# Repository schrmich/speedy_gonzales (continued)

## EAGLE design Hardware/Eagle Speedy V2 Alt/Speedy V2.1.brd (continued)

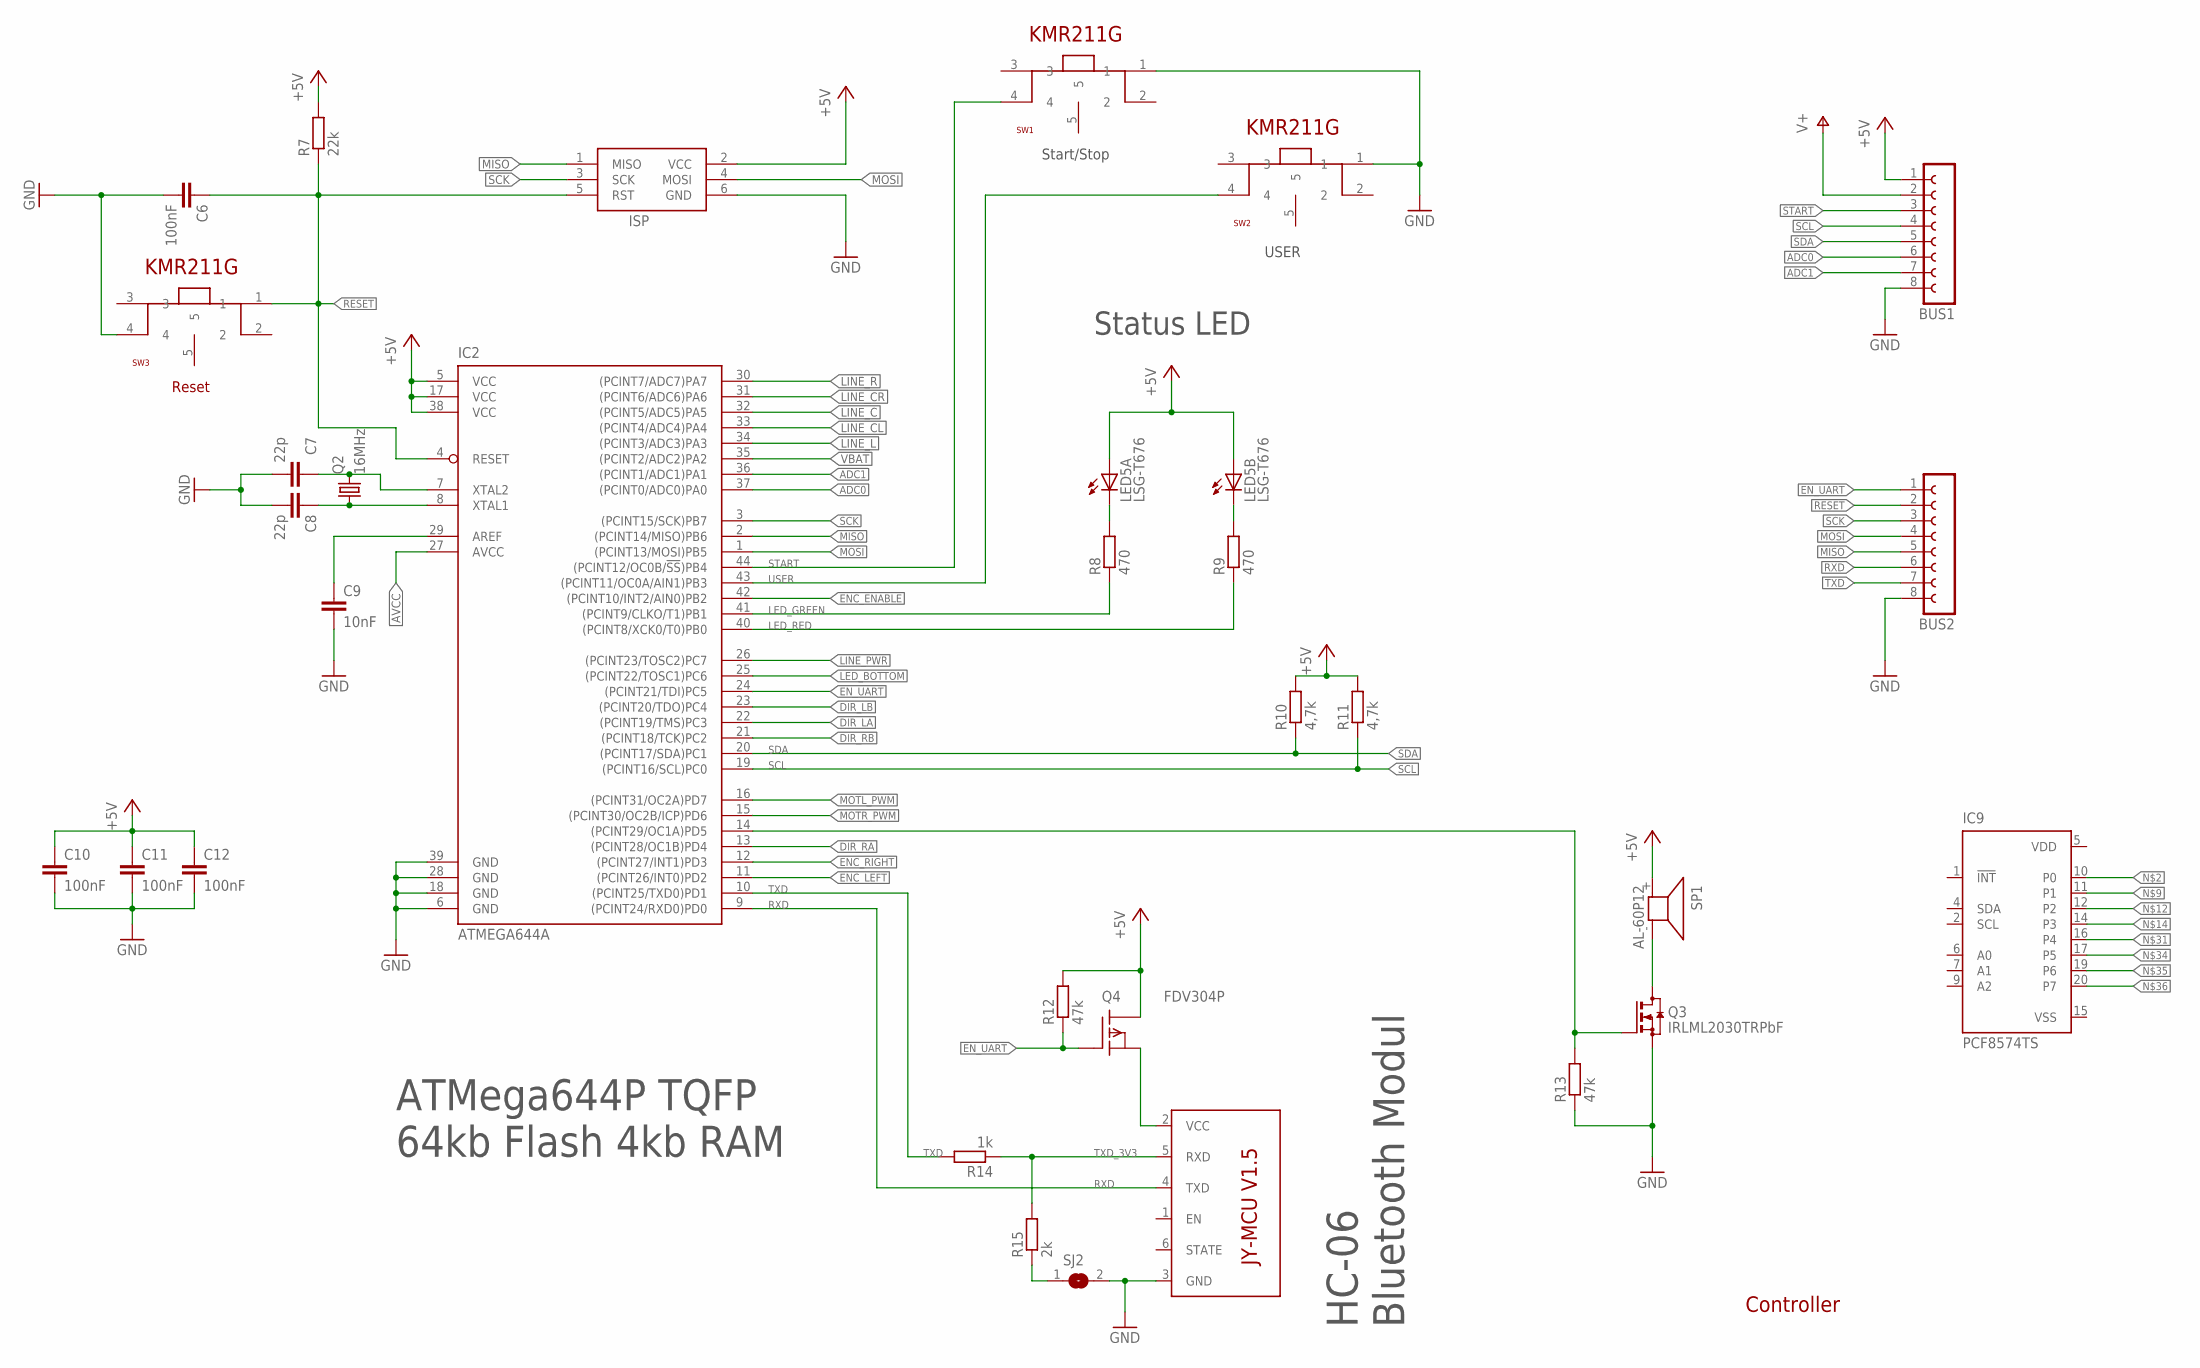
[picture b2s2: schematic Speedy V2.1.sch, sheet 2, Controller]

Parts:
BUS1, BUS2: FE08-1; FE08
C6: 100nF; C0805
C7, C8: 22p; C0603
C9: 10nF; C0603
C10, C11, C12: 100nF; C0603
IC2: ATMEGA644A; TQFP44
IC9: PCF8574TS; SSOP20
ISP: AVRISP-6; AVRISP
LED5: LSG-T676; P-LCC4-0
Q2: 16MHz; 7X5MMQUARZ
Q3: IRLML2030TRPbF; SOT23
Q4: FDV304P; SOT23
R7: 22k; R0805
R8, R9: 470; R0805
R10, R11: 4,7k; R0805
R12, R13: 47k; R0805
R14: 1k; R0805
R15: 2k; R0805
SJ2: SJ
SP1: AL-60P12; KSS1201
SW1, SW2, SW3: KMR211G_SWITCH
U1: BT_BOARD

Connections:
+5V: BUS1.1, C10.1, C11.1, C12.1, IC2.5 (VCC), IC2.17 (VCC), IC2.38 (VCC), ISP.2 (VCC), LED5.2 (A), LED5.4 (A), Q4.D, R7.2, R10.2, R11.2, R12.2, SP1.+ (1); also elsewhere on the board
ADC0: BUS1.6, IC2.37 ((PCINT0/ADC0)PA0)
ADC1: BUS1.7, IC2.36 ((PCINT1/ADC1)PA1)
AVCC: IC2.27 (AVCC); also elsewhere on the board
BUZZER: IC2.14 ((PCINT29/OC1A)PD5), Q3.1 (G), R13.2
DIR_LA: IC2.22 ((PCINT19/TMS)PC3); also elsewhere on the board
DIR_LB: IC2.23 ((PCINT20/TDO)PC4); also elsewhere on the board
DIR_RA: IC2.13 ((PCINT28/OC1B)PD4); also elsewhere on the board
DIR_RB: IC2.21 ((PCINT18/TCK)PC2); also elsewhere on the board
ENC_ENABLE: IC2.42 ((PCINT10/INT2/AIN0)PB2)
ENC_LEFT: IC2.11 ((PCINT26/INT0)PD2)
ENC_RIGHT: IC2.12 ((PCINT27/INT1)PD3)
EN_UART: BUS2.1, IC2.24 ((PCINT21/TDI)PC5), Q4.G, R12.1
GND: BUS1.8, BUS2.8, C6.2, C7.2, C8.2, C9.2, C10.2, C11.2, C12.2, IC2.6 (GND), IC2.18 (GND), IC2.28 (GND), IC2.39 (GND), ISP.6 (GND), Q3.2 (S), R13.1, SJ2.2, SW1.1, SW2.1, SW3.4, U1.3 (GND); also elsewhere on the board
LED_BOTTOM: IC2.25 ((PCINT22/TOSC1)PC6); also elsewhere on the board
LED_GREEN: IC2.41 ((PCINT9/CLKO/T1)PB1), R8.1
LED_RED: IC2.40 ((PCINT8/XCK0/T0)PB0), R9.1
LINE_C: IC2.32 ((PCINT5/ADC5)PA5); also elsewhere on the board
LINE_CL: IC2.33 ((PCINT4/ADC4)PA4); also elsewhere on the board
LINE_CR: IC2.31 ((PCINT6/ADC6)PA6); also elsewhere on the board
LINE_L: IC2.34 ((PCINT3/ADC3)PA3); also elsewhere on the board
LINE_PWR: IC2.26 ((PCINT23/TOSC2)PC7); also elsewhere on the board
LINE_R: IC2.30 ((PCINT7/ADC7)PA7); also elsewhere on the board
MISO: BUS2.5, IC2.2 ((PCINT14/MISO)PB6), ISP.1 (MISO)
MOSI: BUS2.4, IC2.1 ((PCINT13/MOSI)PB5), ISP.4 (MOSI)
MOTL_PWM: IC2.16 ((PCINT31/OC2A)PD7); also elsewhere on the board
MOTR_PWM: IC2.15 ((PCINT30/OC2B/ICP)PD6); also elsewhere on the board
unnamed: Q3.3 (D), SP1.- (2)
unnamed: LED5.1 (C), R8.2
unnamed: C9.1, IC2.29 (AREF)
unnamed: R15.1, SJ2.1
unnamed: LED5.3 (C), R9.2
unnamed: Q4.S, U1.2 (VCC)
unnamed: C7.1, IC2.7 (XTAL2), Q2.P$3 (2)
unnamed: C8.1, IC2.8 (XTAL1), Q2.P$1 (1)
RESET: BUS2.2, C6.1, IC2.4 (RESET), ISP.5 (RST), R7.1, SW3.1; also elsewhere on the board
RXD: BUS2.6, IC2.9 ((PCINT24/RXD0)PD0), U1.4 (TXD)
SCK: BUS2.3, IC2.3 ((PCINT15/SCK)PB7), ISP.3 (SCK)
SCL: BUS1.4, IC2.19 ((PCINT16/SCL)PC0), R11.1
SDA: BUS1.5, IC2.20 ((PCINT17/SDA)PC1), R10.1
START: BUS1.3, IC2.44 ((PCINT12/OC0B/!SS!)PB4), SW1.4
TXD: BUS2.7, IC2.10 ((PCINT25/TXD0)PD1), R14.2
TXD_3V3: R14.1, R15.2, U1.5 (RXD)
USER: IC2.43 ((PCINT11/OC0A/AIN1)PB3), SW2.4
V+: BUS1.2; also elsewhere on the board
VBAT: IC2.35 ((PCINT2/ADC2)PA2); also elsewhere on the board
VDD: IC9.5 (VDD)
VSS: IC9.15 (VSS)

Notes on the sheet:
Controller
Start/Stop
Reset
HC-06 Bluetooth Modul
ATMega644P TQFP 64kb Flash 4kb RAM
USER
Status LED

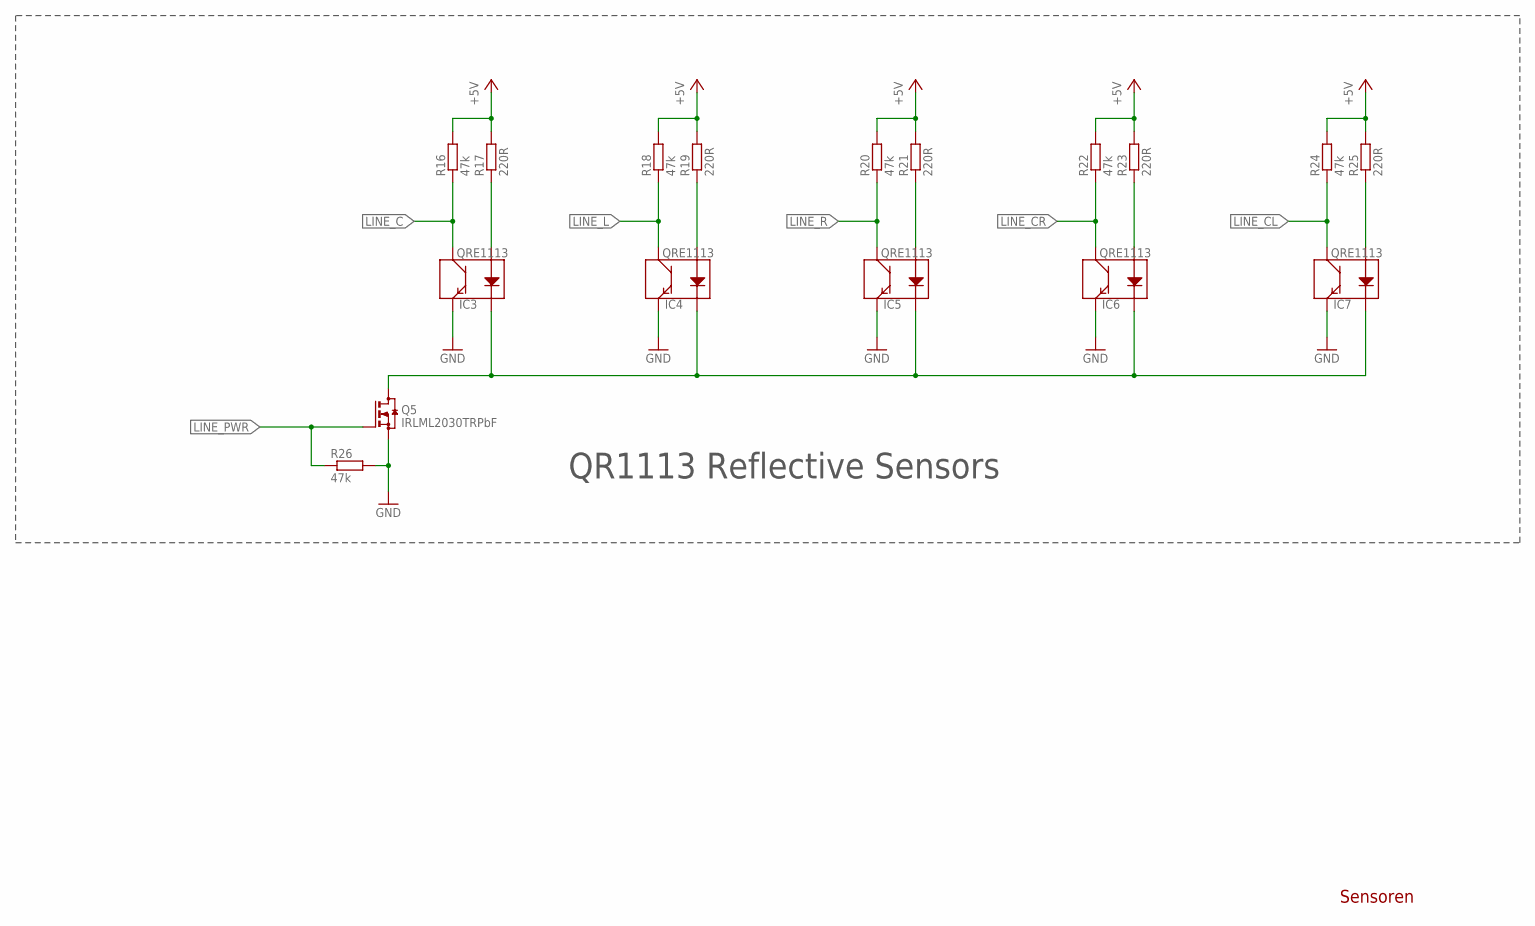
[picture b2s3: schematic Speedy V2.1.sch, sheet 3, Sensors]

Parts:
IC3, IC4, IC5, IC6, IC7: QRE1113
Q5: IRLML2030TRPbF; SOT23
R16, R18, R20, R22, R24, R26: 47k; R0805
R17, R19, R21, R23, R25: 220R; R0805

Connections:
+5V: R16.2, R17.2, R18.2, R19.2, R20.2, R21.2, R22.2, R23.2, R24.2, R25.2; also elsewhere on the board
GND: IC3.4 (E), IC4.4 (E), IC5.4 (E), IC6.4 (E), IC7.4 (E), Q5.2 (S), R26.2; also elsewhere on the board
LINE_C: IC3.3 (C), R16.1; also elsewhere on the board
LINE_CL: IC7.3 (C), R24.1; also elsewhere on the board
LINE_CR: IC6.3 (C), R22.1; also elsewhere on the board
LINE_L: IC4.3 (C), R18.1; also elsewhere on the board
LINE_PWR: Q5.1 (G), R26.1; also elsewhere on the board
LINE_R: IC5.3 (C), R20.1; also elsewhere on the board
unnamed: IC3.2 (K), IC4.2 (K), IC5.2 (K), IC6.2 (K), IC7.2 (K), Q5.3 (D)
unnamed: IC4.1 (A), R19.1
unnamed: IC3.1 (A), R17.1
unnamed: IC5.1 (A), R21.1
unnamed: IC6.1 (A), R23.1
unnamed: IC7.1 (A), R25.1

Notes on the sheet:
Sensoren
QR1113 Reflective Sensors

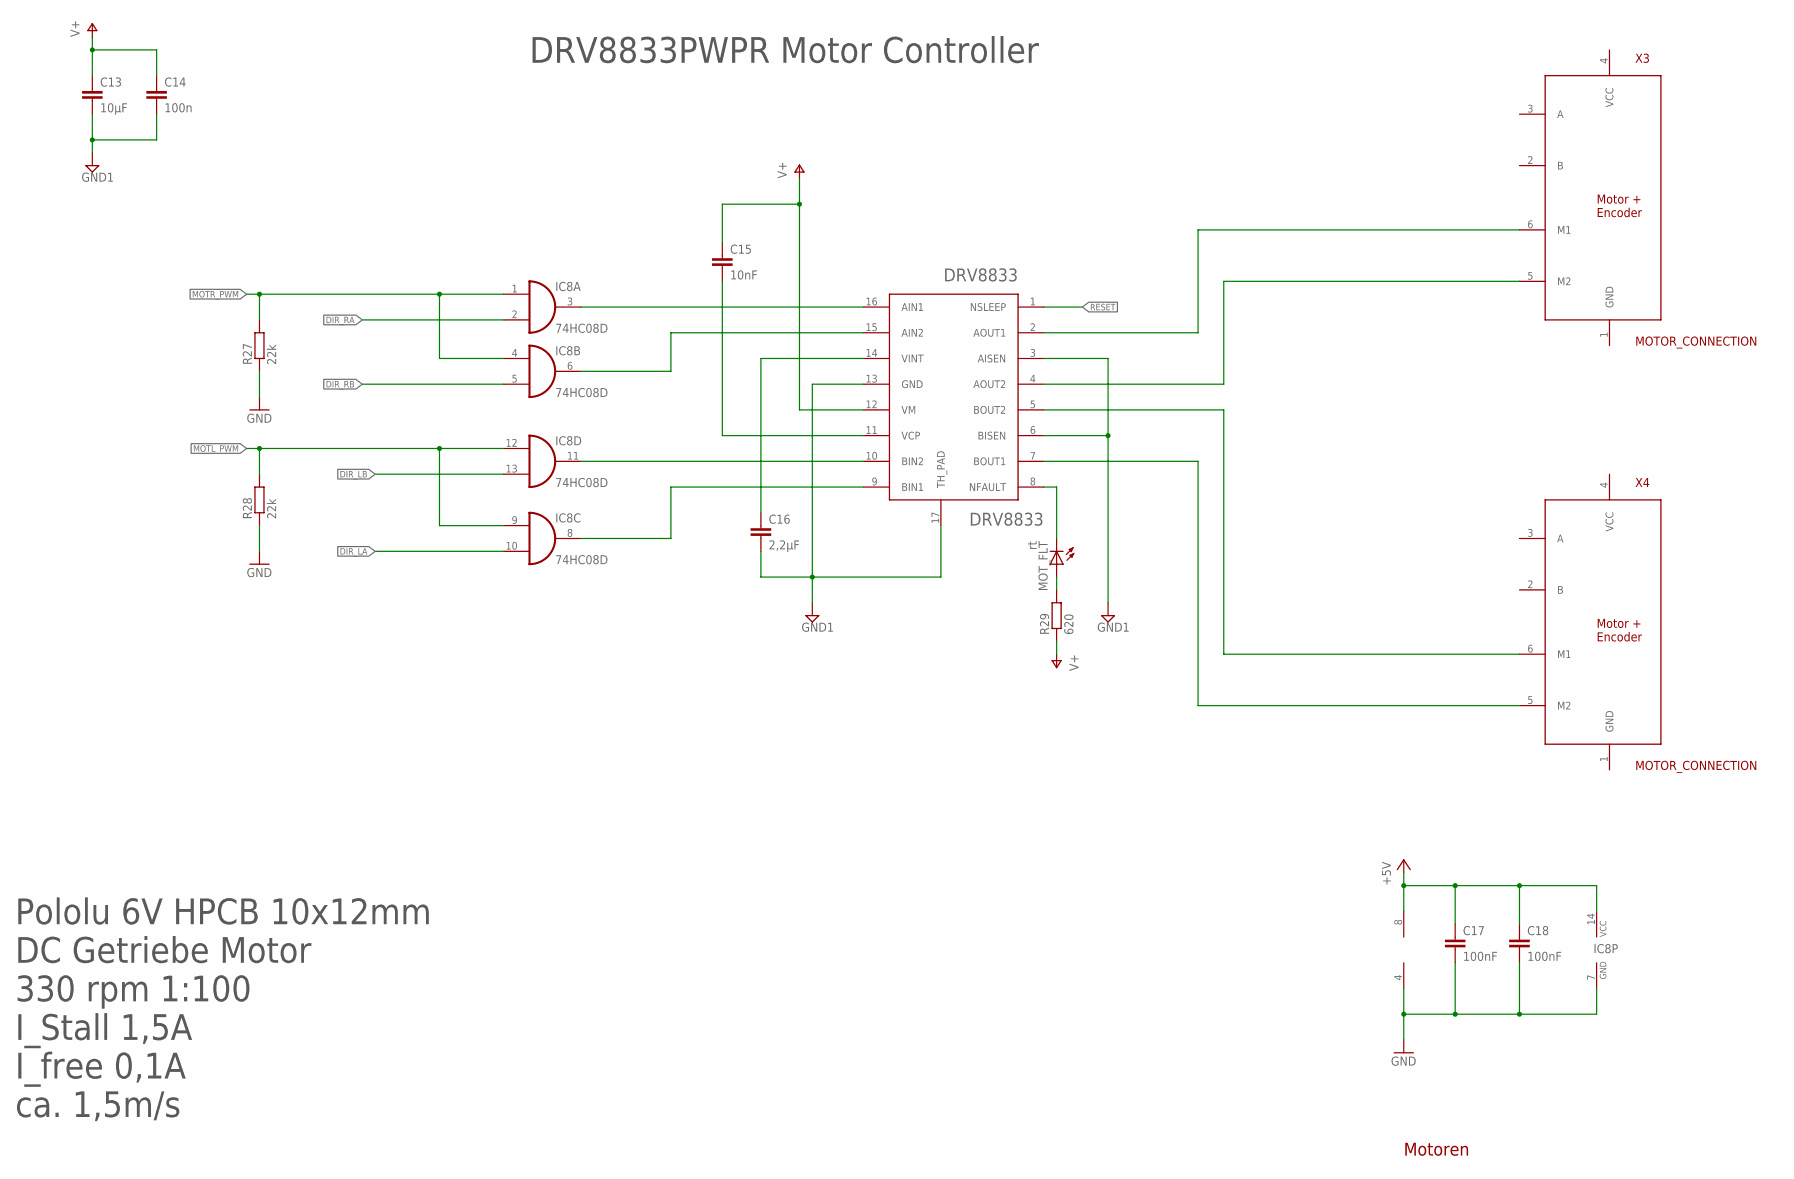
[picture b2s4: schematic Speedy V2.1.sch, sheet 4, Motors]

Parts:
C13: 10µF; C1206
C14: 100n; C0805
C15: 10nF; C0805
C16: 2,2µF; C1206
C17, C18: 100nF; C0805
IC8: 74HC08D; SO14
IC11: LM358D; SO08
MOT_FLT: rt; CHIP-LED0805
R27, R28: 22k; R0805
R29: 620; R0805
U3: DRV8833; SOP65P640X120-17N
X3, X4: MOTOR_CONNECTION; 2X03

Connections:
+5V: C17.1, C18.1, IC8.14 (VCC), IC11.8 (V+); also elsewhere on the board
DIR_LA: IC8.10 (I1); also elsewhere on the board
DIR_LB: IC8.13 (I1); also elsewhere on the board
DIR_RA: IC8.2 (I1); also elsewhere on the board
DIR_RB: IC8.5 (I1); also elsewhere on the board
GND: C17.2, C18.2, IC8.7 (GND), IC11.4 (V-), R27.1, R28.1; also elsewhere on the board
GND1: C13.2, C14.2, C16.2, U3.3 (AISEN), U3.6 (BISEN), U3.13 (GND), U3.17 (TH_PAD); also elsewhere on the board
MOTL_PWM: IC8.9 (I0), IC8.12 (I0), R28.2; also elsewhere on the board
MOTR_PWM: IC8.1 (I0), IC8.4 (I0), R27.2; also elsewhere on the board
unnamed: C16.1, U3.14 (VINT)
unnamed: C15.2, U3.11 (VCP)
unnamed: U3.5 (BOUT2), X4.6 (M1)
unnamed: MOT_FLT.A, R29.2
unnamed: MOT_FLT.C, U3.8 (NFAULT)
unnamed: IC8.3 (O), U3.16 (AIN1)
unnamed: IC8.6 (O), U3.15 (AIN2)
unnamed: IC8.11 (O), U3.10 (BIN2)
unnamed: IC8.8 (O), U3.9 (BIN1)
unnamed: U3.7 (BOUT1), X4.5 (M2)
unnamed: U3.4 (AOUT2), X3.5 (M2)
unnamed: U3.2 (AOUT1), X3.6 (M1)
RESET: U3.1 (NSLEEP); also elsewhere on the board
V+: C13.1, C14.1, C15.1, R29.1, U3.12 (VM); also elsewhere on the board

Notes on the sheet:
Motoren
DRV8833PWPR Motor Controller
Pololu 6V HPCB 10x12mm DC Getriebe Motor 330 rpm 1:100 I_Stall 1,5A I_free 0,1A ca. 1,5m/s

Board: 2 copper layers, 91 parts (23 on the bottom side), 71 nets, no tracks yet.

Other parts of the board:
U$1: FUTURA_V1.0_MOTOT_MOUNT

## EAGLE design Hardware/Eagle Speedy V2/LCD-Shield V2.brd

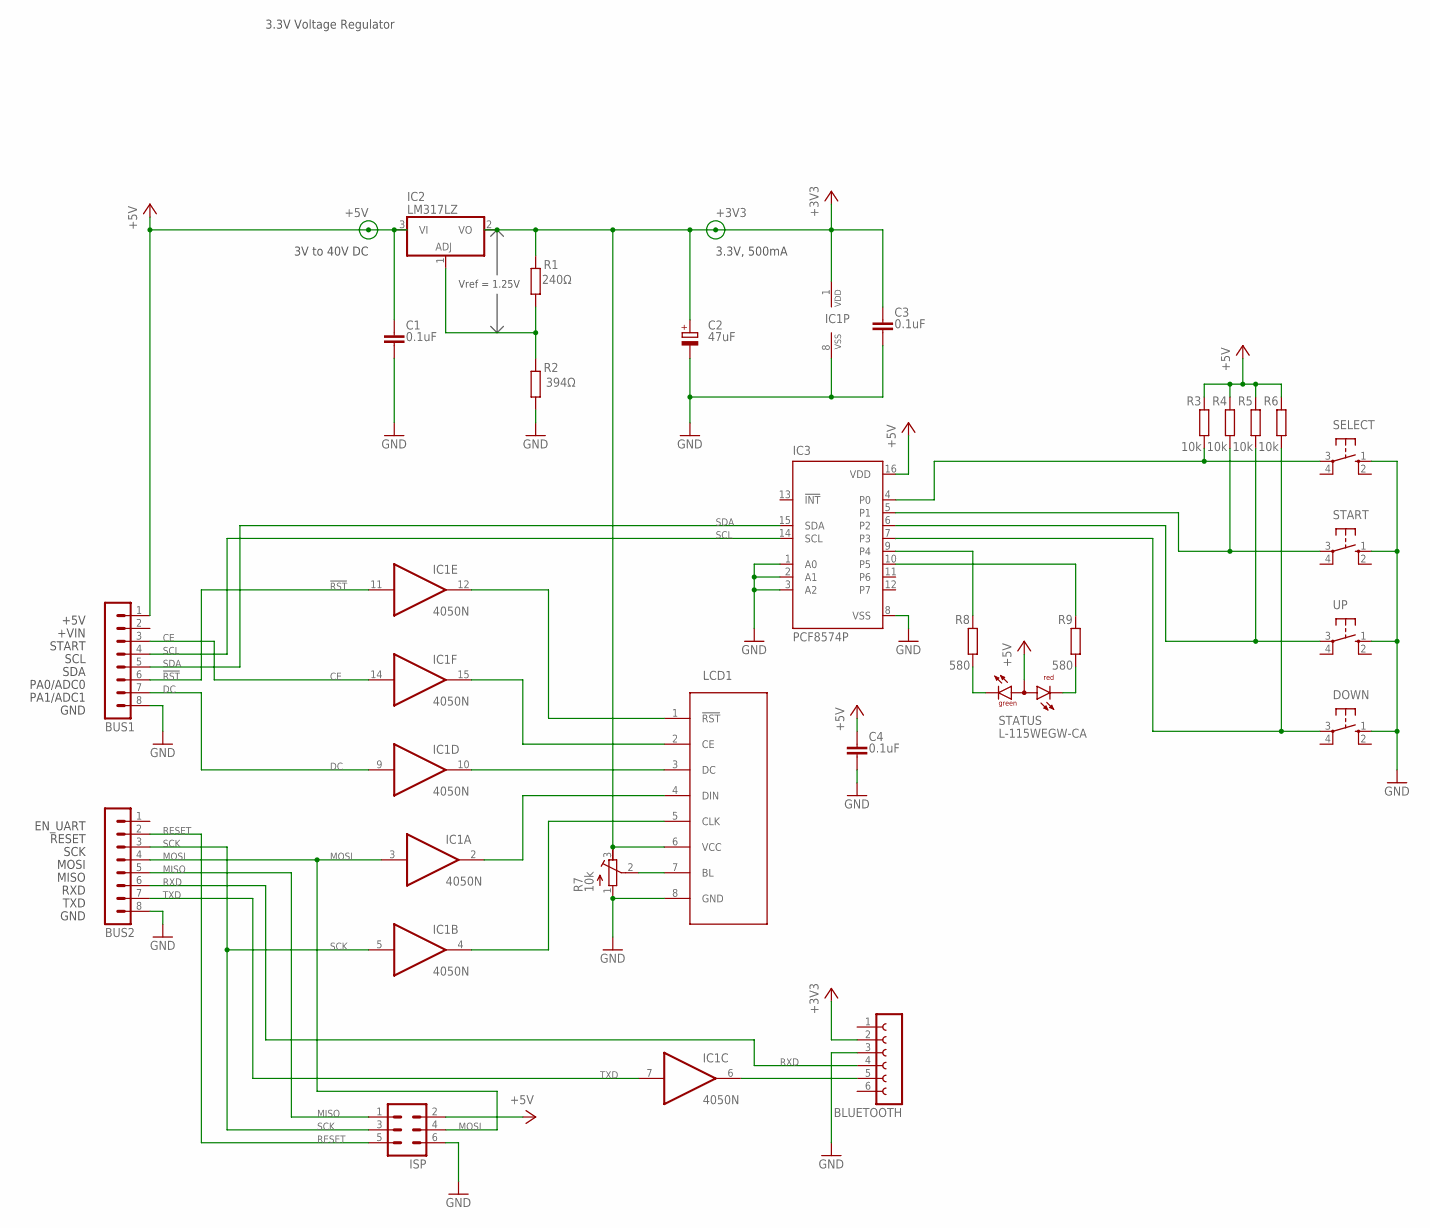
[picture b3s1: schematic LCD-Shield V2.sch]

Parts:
BLUETOOTH: FE06-1; FE06
BUS1, BUS2: MA08-1
C1, C3, C4: 0.1uF; C025-024X044
C2: 47uF; E2-4
DOWN: 10-XX; B3F-10XX
IC1: 4050N; DIL16
IC2: LM317LZ; TO92
IC3: PCF8574P; DIL16
ISP: MA03-2
LCD1: 5110_LCD_NOKIA; LCD_5110
R1: 240Ω; 0207/7
R2: 394Ω; 0207/7
R3, R4, R5, R6: 10k; 0207/7
R7: 10k; RTRIM3296W
R8, R9: 580; 0207/7
SELECT: 10-XX; B3F-10XX
START: 10-XX; B3F-10XX
STATUS: L-115WEGW-CA; DUOLED-A-3MM
UP: 10-XX; B3F-10XX

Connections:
!RST: BUS1.6, IC1.11 (I)
+3V3: BLUETOOTH.2, C2.+, C3.1, IC1.1 (VDD), IC2.2 (VO), LCD1.6 (VCC), R1.2, R7.3 (E)
+5V: BUS1.1, C1.1, C4.1, IC2.3 (VI), IC3.16 (VDD), ISP.2, R3.2, R4.2, R5.2, R6.2, STATUS.2 (A)
CE: BUS1.3, IC1.14 (I)
DC: BUS1.7, IC1.9 (I)
GND: BLUETOOTH.3, BUS1.8, BUS2.8, C1.2, C2.-, C3.2, C4.2, DOWN.1 (S), IC1.8 (VSS), IC3.1 (A0), IC3.2 (A1), IC3.3 (A2), IC3.8 (VSS), ISP.6, LCD1.8 (GND), R2.1, R7.1 (A), SELECT.1 (S), START.1 (S), UP.1 (S)
MISO: BUS2.5, ISP.1
MOSI: BUS2.4, IC1.3 (I), ISP.4
unnamed: IC1.12 (O), LCD1.1 (!RST)
unnamed: IC1.15 (O), LCD1.2 (CE)
unnamed: IC1.10 (O), LCD1.3 (DC)
unnamed: IC1.2 (O), LCD1.4 (DIN)
unnamed: IC1.4 (O), LCD1.5 (CLK)
unnamed: IC2.1 (ADJ), R1.1, R2.2
unnamed: R8.1, STATUS.1 (CG)
unnamed: LCD1.7 (BL), R7.2 (S)
unnamed: R9.1, STATUS.3 (CR)
unnamed: IC3.9 (P4), R8.2
unnamed: IC3.10 (P5), R9.2
unnamed: IC3.4 (P0), R3.1, SELECT.3
unnamed: IC3.5 (P1), R4.1, START.3
unnamed: IC3.6 (P2), R5.1, UP.3
unnamed: DOWN.3, IC3.7 (P3), R6.1
unnamed: BLUETOOTH.5, IC1.6 (O)
RESET: BUS2.2, ISP.5
RXD: BLUETOOTH.4, BUS2.6
SCK: BUS2.3, IC1.5 (I), ISP.3
SCL: BUS1.4, IC3.14 (SCL)
SDA: BUS1.5, IC3.15 (SDA)
TXD: BUS2.7, IC1.7 (I)

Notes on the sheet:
3.3V Voltage Regulator
3V to 40V DC
Vref = 1.25V
3.3V, 500mA
+5V
+VIN
START
SCL
SDA
PA0/ADC0
PA1/ADC1
GND
EN_UART
RESET
SCK
MOSI
MISO
RXD
TXD

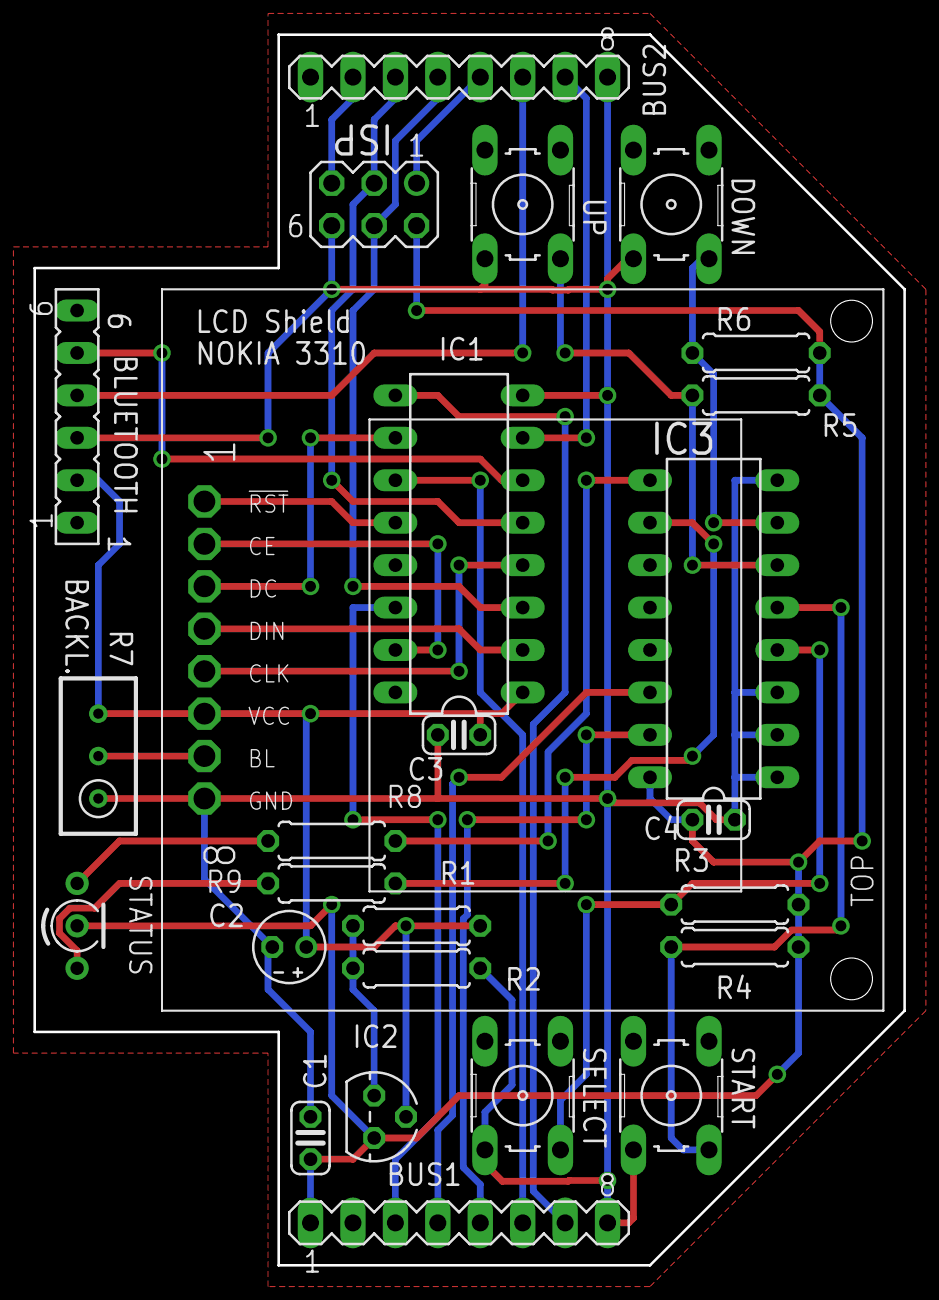
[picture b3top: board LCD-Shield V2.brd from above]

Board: 2 copper layers, 52.1 x 73.7 mm, 26 parts (0 on the bottom side), 30 nets.

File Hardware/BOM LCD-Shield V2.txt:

Qty	Value	Device	Package	Parts	Description
1		FE06-1	FE06	BLUETOOTH	FEMALE HEADER
2		MA08-1	MA08-1	BUS1, BUS2	PIN HEADER
3	0.1uF	C-EU025-024X044	C025-024X044	C1, C3, C4	CAPACITOR, European symbol
1	47uF	CPOL-EUE2-4	E2-4	C2	POLARIZED CAPACITOR, European
4		10-XX	B3F-10XX	DOWN, SELECT, START, UP	OMRON SWITCH
1	4050N	4050N	DIL16	IC1	Hex non-inverting BUFFER
1	LM317LZ	LM317LZ	TO92	IC2	Positive VOLTAGE REGULATOR
1	PCF8574P	PCF8574P	DIL16	IC3	I2C-Bus Remote 8-bit I/O expa
1		MA03-2	MA03-2	ISP	PIN HEADER
1	5110_LCD_NOKIA	5110_LCD_NOKIA	LCD_5110	LCD1	
1	240?	R-EU_0207/7	0207/7	R1	RESISTOR, European symbol
1	394?	R-EU_0207/7	0207/7	R2	RESISTOR, European symbol
4	10k	R-EU_0207/7	0207/7	R3, R4, R5,R6	RESISTOR, European symbol
1	10k	R-TRIMM3296W	RTRIM3296W	R7	Trimm resistor
2	580	R-EU_0207/7	0207/7	R8, R9	RESISTOR, European symbol
1	L-115WEGW-CA	L-115WEGW-CA	DUOLED-A-3MM	STATUS	T-1(3mm) BI-COLOR INDICATOR L

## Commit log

2021-03-15 Test
